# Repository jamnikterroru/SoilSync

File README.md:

# SoilSync
An IoT-based distributed irrigation system featuring an STM32 sensor node, Arduino R4 WiFi gateway, and NRF24L01 wireless telemetry.

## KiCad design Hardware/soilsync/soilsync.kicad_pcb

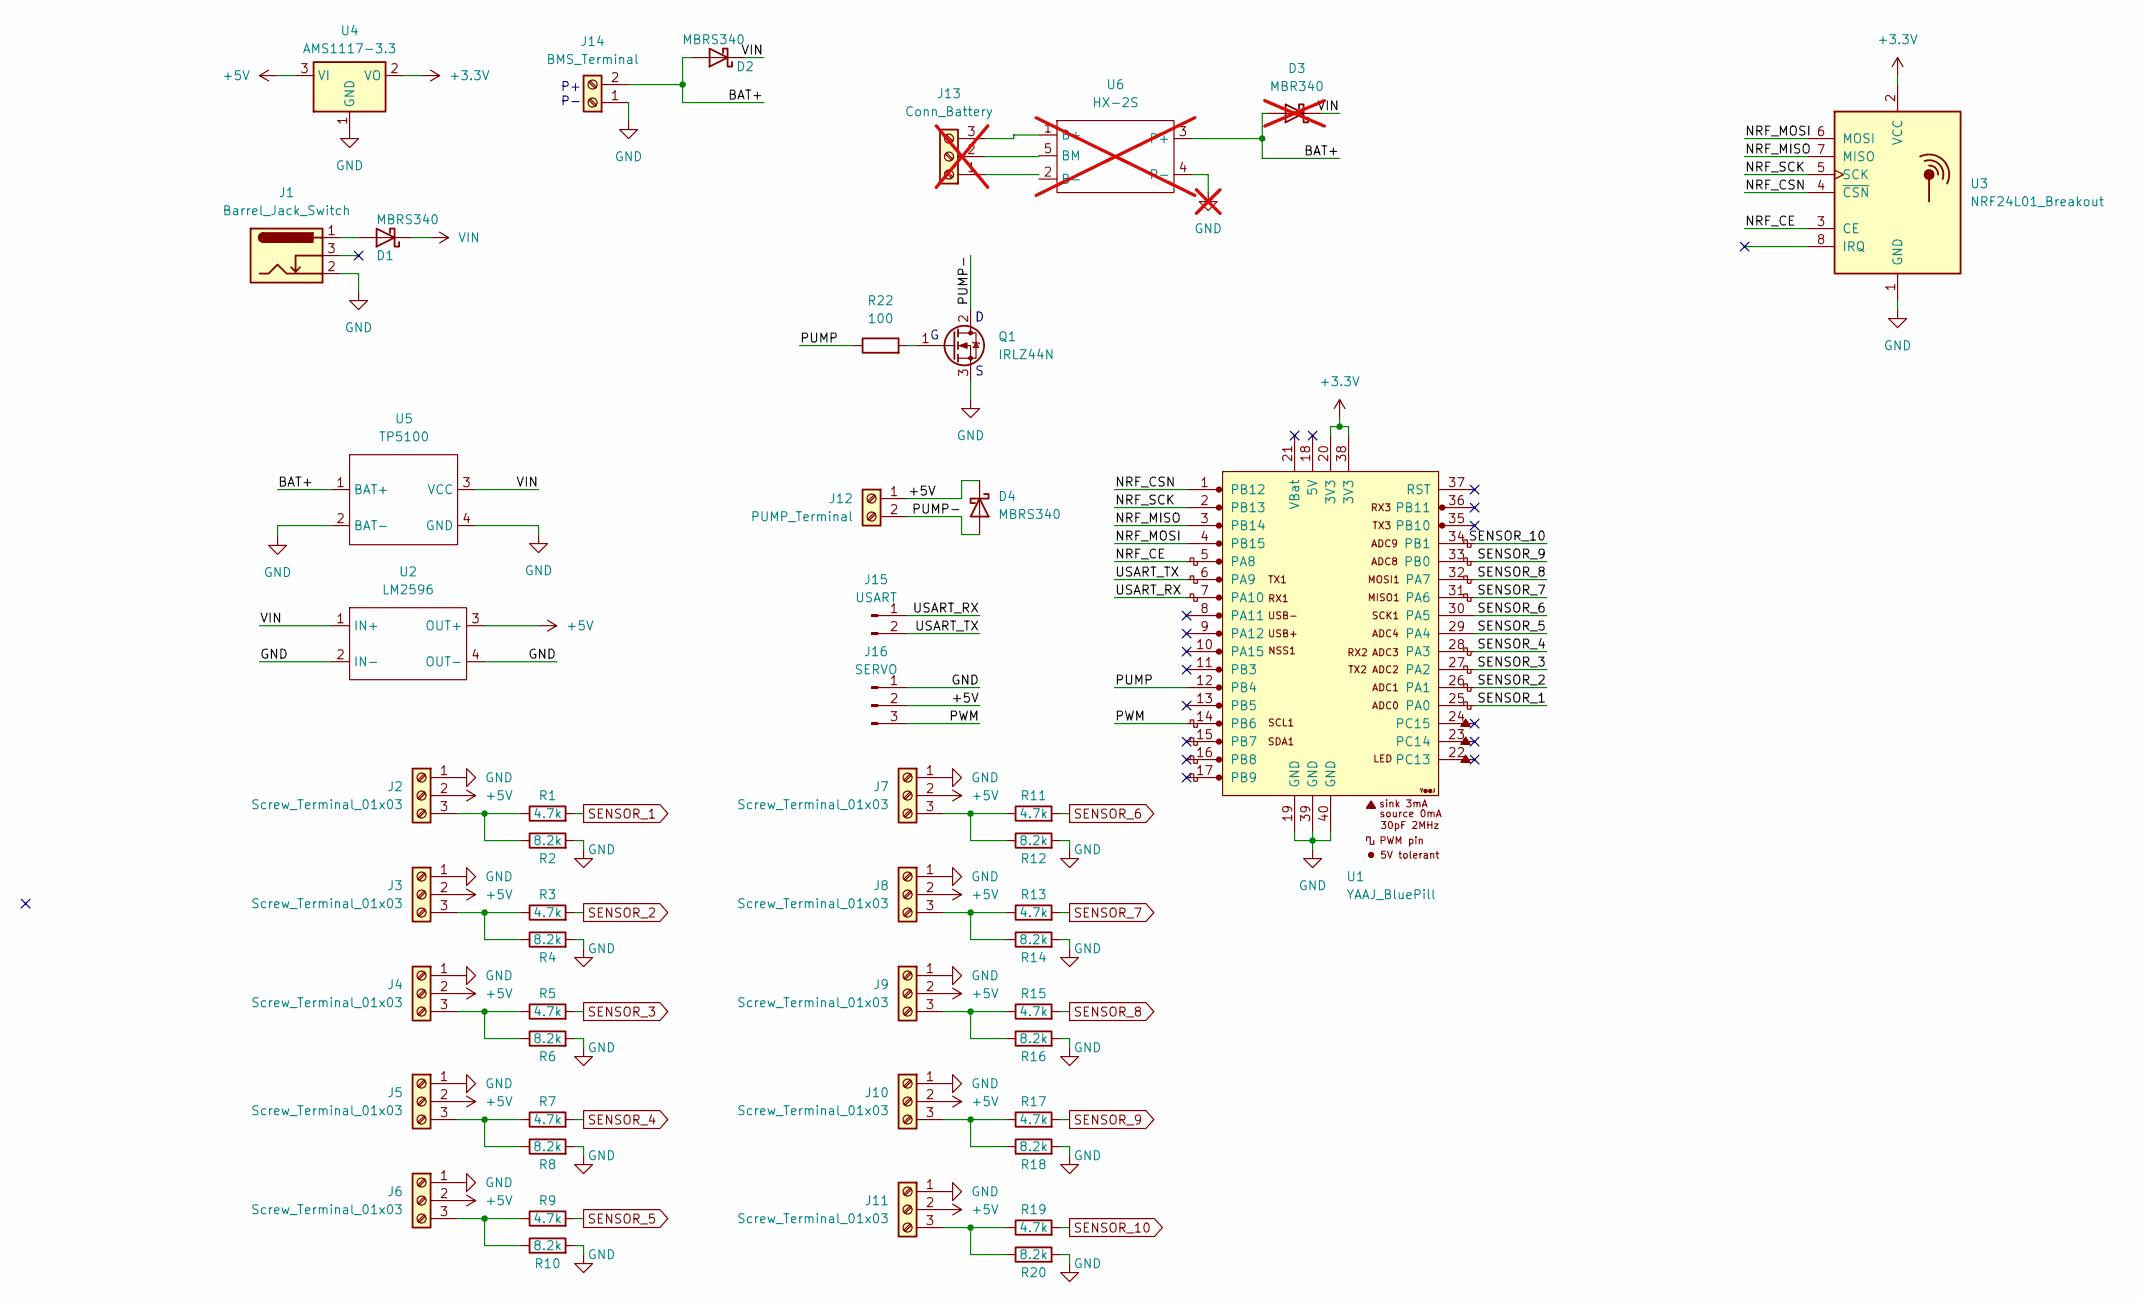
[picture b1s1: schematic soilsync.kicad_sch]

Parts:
D1, D2, D4: MBRS340; D_SMC
D3: MBR340; D_DO-201AD_P15.24mm_Horizontal; not fitted
J1: Barrel_Jack_Switch; BarrelJack_Horizontal
J2, J3, J4, J5, J6, J7, J8, J9, J10, J11: Screw_Terminal_01x03; TerminalBlock_4Ucon_1x03_P3.50mm_Horizontal
J12: PUMP_Terminal; TerminalBlock_4Ucon_1x02_P3.50mm_Horizontal
J13: Conn_Battery; TerminalBlock_4Ucon_1x03_P3.50mm_Horizontal; not fitted
J14: BMS_Terminal; TerminalBlock_4Ucon_1x02_P3.50mm_Horizontal
J15: USART; PinHeader_1x02_P2.54mm_Vertical
J16: SERVO; PinHeader_1x03_P2.54mm_Vertical
Q1: IRLZ44N; TO-220-3_Vertical
R1, R3, R5, R7, R9, R11, R13, R15, R17, R19: 4.7k; R_0805_2012Metric
R2, R4, R6, R8, R10, R12, R14, R16, R18, R20: 8.2k; R_0805_2012Metric
R22: 100; R_1206_3216Metric_Pad1.30x1.75mm_HandSolder
U1: YAAJ_BluePill; YAAJ_BluePill_1
U2: LM2596; LM2596 module
U3: NRF24L01_Breakout; nRF24L01_Breakout
U4: AMS1117-3.3; SOT-223-3_TabPin2
U5: TP5100; TP5100_Module
U6: HX-2S; HX-2S BMS module; not fitted

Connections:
+3.3V: U1.20 (3V3), U1.38 (3V3), U3.2 (VCC), U4.2 (VO)
+5V: D4.1 (K), J2.2, J3.2, J4.2, J5.2, J6.2, J7.2, J8.2, J9.2, J10.2, J11.2, J12.1, J16.2, U2.3 (OUT+), U4.3 (VI)
/BAT+: D2.2 (A), D3.2 (A), J14.2, U5.1 (BAT+), U6.3 (P+)
/NRF_CE: U1.5 (PA8), U3.3 (CE)
/NRF_CSN: U1.1 (PB12), U3.4 (~CSN)
/NRF_MISO: U1.3 (PB14), U3.7 (MISO)
/NRF_MOSI: U1.4 (PB15), U3.6 (MOSI)
/NRF_SCK: U1.2 (PB13), U3.5 (SCK)
/PUMP: R22.1, U1.12 (PB4)
/PUMP-: D4.2 (A), J12.2, Q1.2 (D)
/PWM: J16.3, U1.14 (PB6)
/USART_RX: J15.1, U1.7 (PA10)
/USART_TX: J15.2, U1.6 (PA9)
GND: J1.2, J2.1, J3.1, J4.1, J5.1, J6.1, J7.1, J8.1, J9.1, J10.1, J11.1, J14.1, J16.1, Q1.3 (S), R2.2, R4.2, R6.2, R8.2, R10.2, R12.2, R14.2, R16.2, R18.2, R20.2, U1.19 (GND), U1.39 (GND), U1.40 (GND), U2.2 (IN-), U2.4 (OUT-), U3.1 (GND), U4.1 (GND), U5.2 (BAT-), U5.4 (GND), U6.4 (P-)
unnamed: D1.2 (A), J1.1
unnamed: J2.3, R1.1, R2.1
unnamed: J3.3, R3.1, R4.1
unnamed: J4.3, R5.1, R6.1
unnamed: J5.3, R7.1, R8.1
unnamed: J6.3, R9.1, R10.1
unnamed: J7.3, R11.1, R12.1
unnamed: J8.3, R13.1, R14.1
unnamed: J9.3, R15.1, R16.1
unnamed: J10.3, R17.1, R18.1
unnamed: J11.3, R19.1, R20.1
unnamed: J13.3, U6.1 (B+)
unnamed: Q1.1 (G), R22.2
SENSOR_1: R1.2, U1.25 (PA0)
SENSOR_2: R3.2, U1.26 (PA1)
SENSOR_3: R5.2, U1.27 (PA2)
SENSOR_4: R7.2, U1.28 (PA3)
SENSOR_5: R9.2, U1.29 (PA4)
SENSOR_6: R11.2, U1.30 (PA5)
SENSOR_7: R13.2, U1.31 (PA6)
SENSOR_8: R15.2, U1.32 (PA7)
SENSOR_9: R17.2, U1.33 (PB0)
SENSOR_10: R19.2, U1.34 (PB1)
VIN: D1.1 (K), D2.1 (K), D3.1 (K), U2.1 (IN+), U5.3 (VCC)

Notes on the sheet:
P+ P-

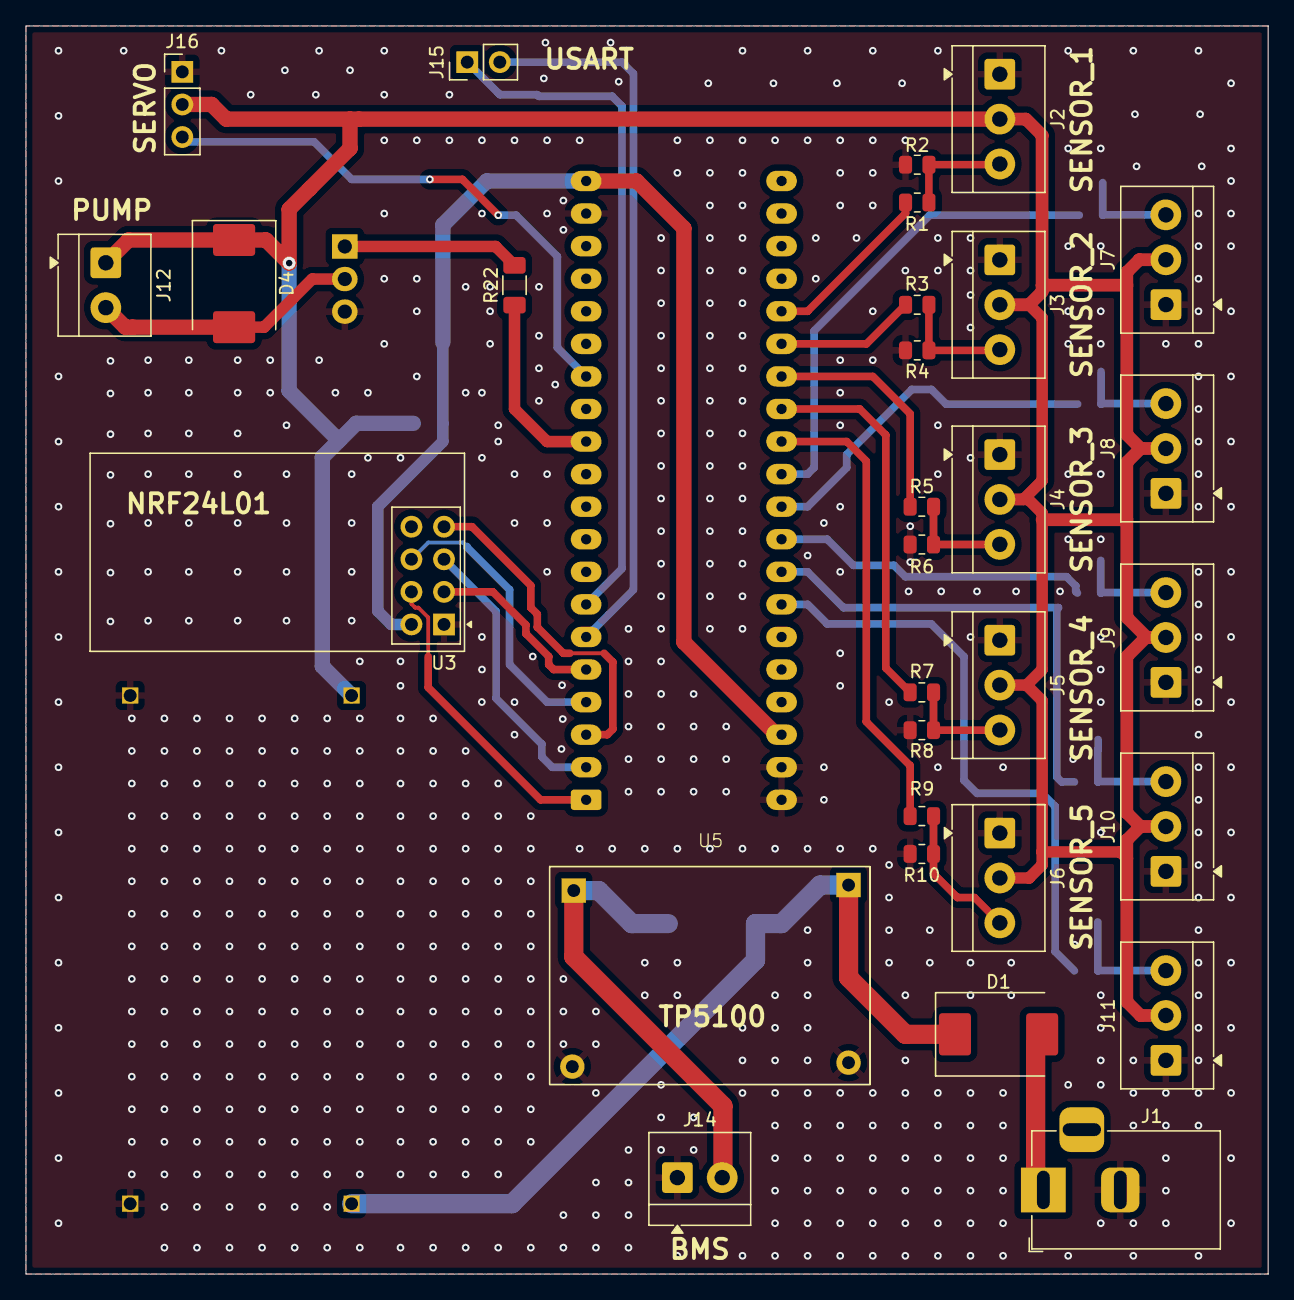
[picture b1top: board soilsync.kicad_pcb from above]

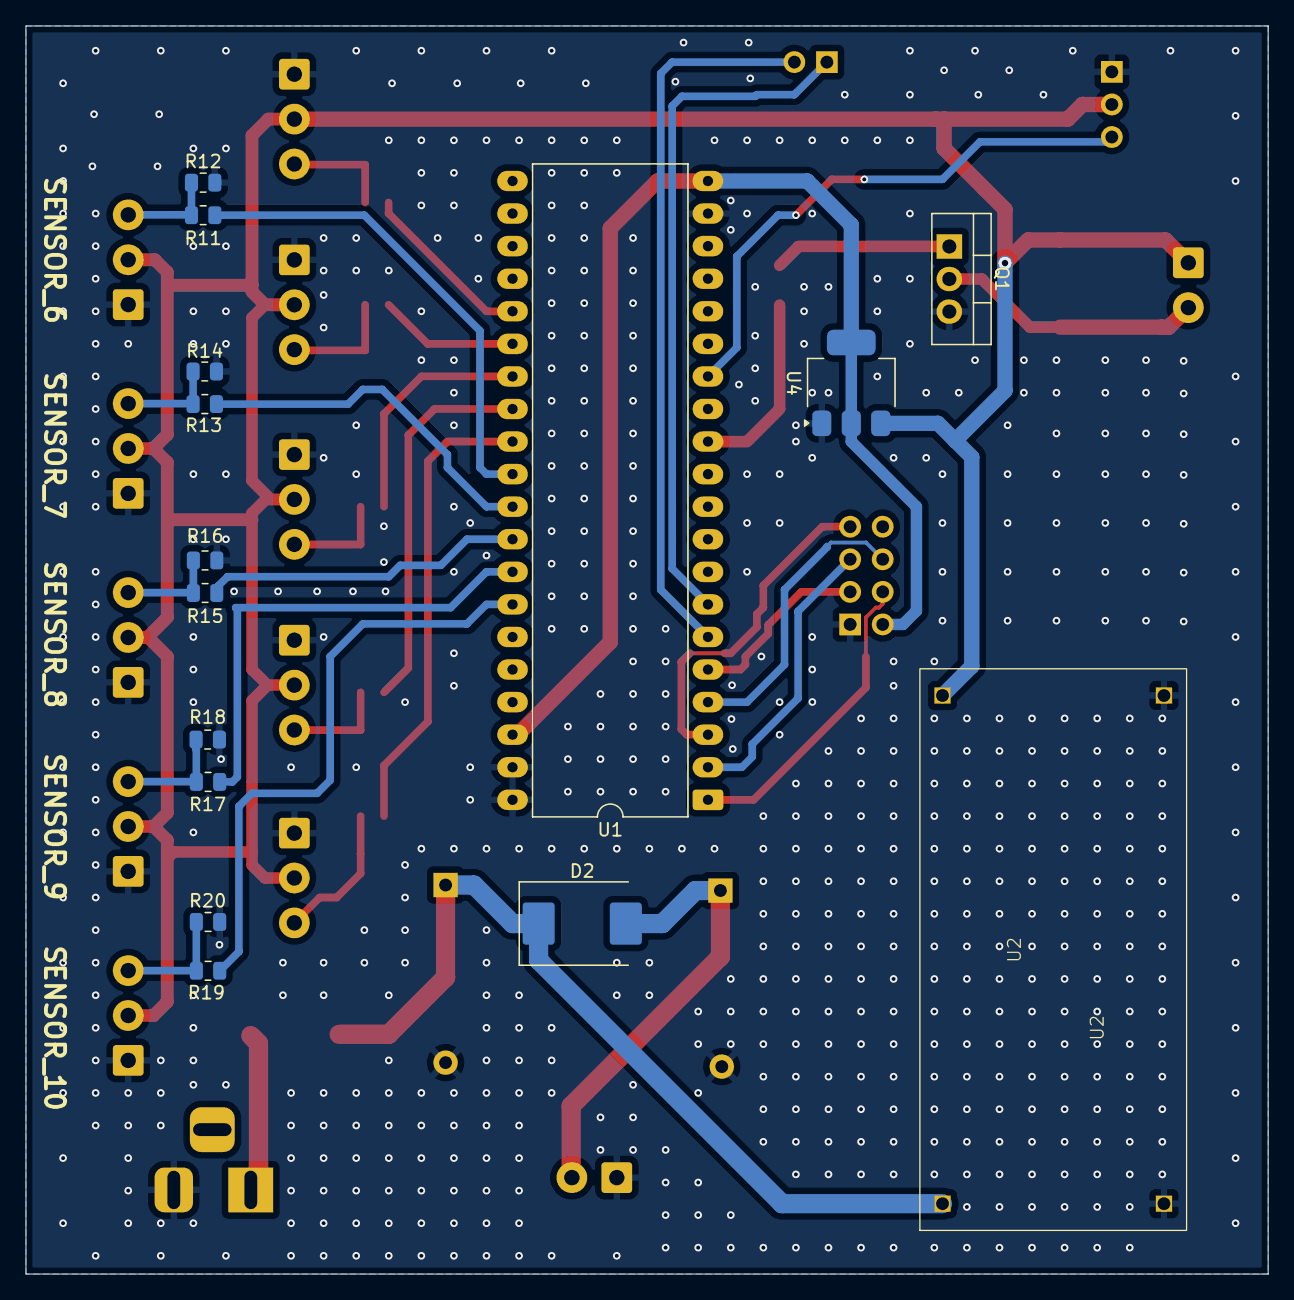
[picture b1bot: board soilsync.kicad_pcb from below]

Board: 2 copper layers, 96.9 x 97.3 mm, 45 parts (15 on the bottom side), 37 nets.

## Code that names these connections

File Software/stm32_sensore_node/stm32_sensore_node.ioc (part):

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Mcu.Name=STM32F103C(8-B)Tx
Mcu.Package=LQFP48
Mcu.UserName=STM32F103C8Tx
PA0-WKUP.Signal=ADCx_IN0
PA1.Signal=ADCx_IN1
PA10.Mode=Asynchronous
PA10.Signal=USART1_RX
PA13.Mode=Serial_Wire
PA13.Signal=SYS_JTMS-SWDIO
PA14.Mode=Serial_Wire
PA14.Signal=SYS_JTCK-SWCLK
PA2.Signal=ADCx_IN2
PA3.Signal=ADCx_IN3
PA4.Signal=ADCx_IN4
PA5.Signal=ADCx_IN5
PA6.Signal=ADCx_IN6
PA7.Signal=ADCx_IN7
PA8.GPIOParameters=GPIO_Label
PA8.GPIO_Label=CE
PA8.Signal=GPIO_Output
PA9.Mode=Asynchronous
PA9.Signal=USART1_TX
PB0.Signal=ADCx_IN8
PB1.Signal=ADCx_IN9
PB12.GPIOParameters=GPIO_Label
PB12.GPIO_Label=CSN
PB12.Signal=GPIO_Output
PB13.Mode=Full_Duplex_Master
PB13.Signal=SPI2_SCK
PB14.Mode=Full_Duplex_Master
PB14.Signal=SPI2_MISO
PB15.Mode=Full_Duplex_Master
PB15.Signal=SPI2_MOSI
PB4.GPIOParameters=GPIO_Label
PB4.GPIO_Label=PUMP
PB4.Signal=GPIO_Output
PB6.Signal=S_TIM4_CH1
PD0-OSC_IN.Mode=HSE-External-Oscillator
PD0-OSC_IN.Signal=RCC_OSC_IN
PD1-OSC_OUT.Mode=HSE-External-Oscillator
PD1-OSC_OUT.Signal=RCC_OSC_OUT
RCC.SYSCLKFreq_VALUE=72000000
RCC.SYSCLKSource=RCC_SYSCLKSOURCE_PLLCLK
board=custom

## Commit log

2026-03-27 Created KiCad project
    Created KiCad project, added custom LM2596 module to library.
2026-03-30 Created CubeMX project
2026-04-10 summary after classes
    failed to create 3D model
2026-05-07 updated in kicad
    added custom components
2026-05-08 a little changes in footprints
2026-05-21 custom components adjustments
2026-05-22 major PCB updates
    placement & routing
2026-05-22 Layout adjustments
    tbf
2026-06-04 finishing PCB
2026-06-05 layout nearly finished.
    need to add mosfet and programming connector
2026-06-06 PCB Finished
    Generated fabrication data
2026-06-06 added Servo pin headers
